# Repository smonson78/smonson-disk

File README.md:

# Smonson Disk
SD card (2x) to ACSI hard drive interface.

This project aims to develop a reliable and useful hard drive solution for Atari ST with two SD card sockets and a
battery-backed clock, satisfying the ACSI protocol, voltage, and timing requirements as given in available specifications.

Features:
- FPGA-controlled ACSI interface to ensure timing conforms to the specification
- One front-mounted removable SD card socket
- One internally-mounted microSD card socket
- SD cards running on a 24MHz SPI bus
- Battery-backed real-time clock
- GUI configuration from ST (once someone writes it...)
- Open-source, so if you want a feature all you have to do is write it and fit it into the 8KB of code space that is currently left!

## How to build and upload:

### Building the microcontroller firmware:
#### Prerequisites
You will need to install:
- A version of GCC that includes support for `avr128da` microcontrollers, cross-compiled for AVR (e.g. 5.4.0).
- A very recent version of avr-libc that has support for `avr128da` microcontrollers - https://www.nongnu.org/avr-libc/. You may need to get this from their github repo.
- A copy of the avr128da "atpack" from Microchip - go to https://packs.download.microchip.com/ and search for `avr128da`; "
Microchip AVR-Dx Series Device Support (2.4.286)" will pop open. Download this file, then change the file extension to `.zip` 
and unzip it into the directory `mcu-source/atpack`.
- (if you are using an Arduino as a programmer) A copy of jtag2updi from the githup repo here: https://github.com/ElTangas/jtag2updi. You will already have this on your system from when you programmed the device.

#### Building
1. Inside `mcu-source`:
1. Update the `Makefile` and set up `LIBC` variable to reflect the path to `avr-libc` on your system
1. Update the `AVRDUDE` variable to reflect your programmer setup (probably just the `avrdude.conf` path)
1. With the UPDI programmer connected, build the source and flash the microcontroller with `make flash`

### Building the FPGA configuration ROM image:

#### Prerequisites
You will need to install Quartus Lite which is a free download from Intel, although you will need to create an account.
Make sure you install MAX V family support
You will also need a "USB-Blaster" or compatible programmer.
If using Linux, you will very likely need to install a `udev` "rules" file for the programmer before it'll work.

#### Building
Just open the project in Quartus, go to "start compilation", then after it's compiled, open the programmer tool and program the chip. It should auto-detect the settings. If it doesn't find the USB Blaster hardware then it's probably udev's fault.

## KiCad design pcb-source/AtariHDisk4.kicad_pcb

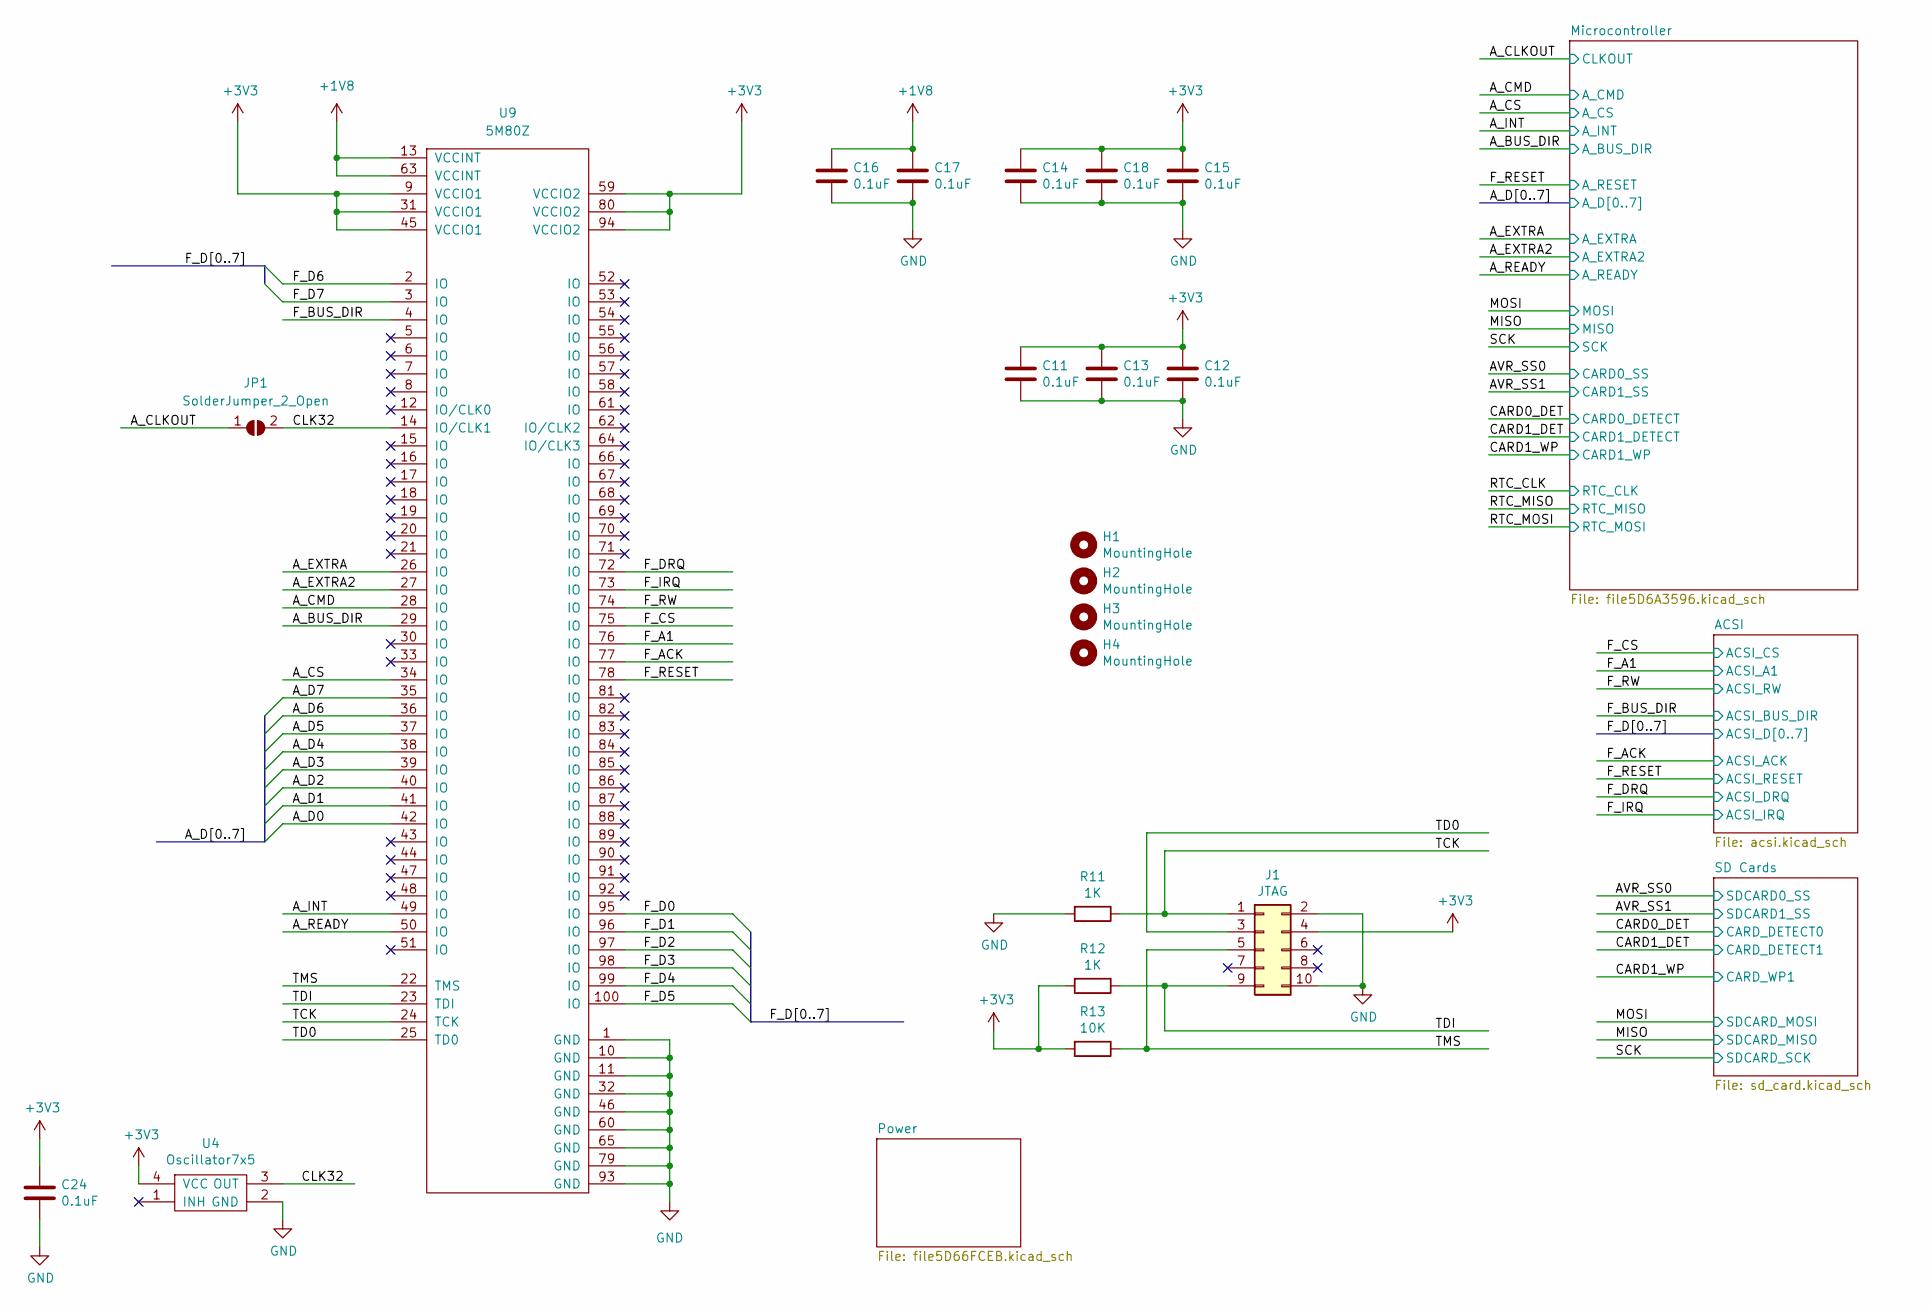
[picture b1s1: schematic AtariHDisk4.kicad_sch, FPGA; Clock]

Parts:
C11, C12, C13, C14, C15, C16, C17, C18, C24: 0.1uF; C_0603_1608Metric
H1, H2, H3, H4: MountingHole; Altronics_H0190_mounting_hole
J1: JTAG; PinHeader_2x05_P2.54mm_Vertical
JP1: SolderJumper_2_Open; SolderJumper-2_P1.3mm_Open_RoundedPad1.0x1.5mm
R11, R12: 1K; R_0805_2012Metric
R13: 10K; R_0805_2012Metric
U4: Oscillator7x5; XO_7x5
U9: 5M80Z; TQFP-100_14x14mm_P0.5mm

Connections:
+1V8: C16.1, C17.1, U9.13 (VCCINT), U9.63 (VCCINT); also elsewhere on the board
+3V3: C11.1, C12.1, C13.1, C14.1, C15.1, C18.1, C24.1, J1.4, R12.2, R13.2, U4.4 (VCC), U9.9 (VCCIO1), U9.31 (VCCIO1), U9.45 (VCCIO1), U9.59 (VCCIO2), U9.80 (VCCIO2), U9.94 (VCCIO2); also elsewhere on the board
/A_BUS_DIR: U9.29 (IO); also elsewhere on the board
/A_CLKOUT: JP1.1 (A); also elsewhere on the board
/A_CMD: U9.28 (IO); also elsewhere on the board
/A_CS: U9.34 (IO); also elsewhere on the board
/A_D0: U9.42 (IO); also elsewhere on the board
/A_D1: U9.41 (IO); also elsewhere on the board
/A_D2: U9.40 (IO); also elsewhere on the board
/A_D3: U9.39 (IO); also elsewhere on the board
/A_D4: U9.38 (IO); also elsewhere on the board
/A_D5: U9.37 (IO); also elsewhere on the board
/A_D6: U9.36 (IO); also elsewhere on the board
/A_D7: U9.35 (IO); also elsewhere on the board
/A_EXTRA: U9.26 (IO); also elsewhere on the board
/A_EXTRA2: U9.27 (IO); also elsewhere on the board
/A_INT: U9.49 (IO); also elsewhere on the board
/A_READY: U9.50 (IO); also elsewhere on the board
/CLK32: JP1.2 (B), U4.3 (OUT), U9.14 (IO/CLK1)
/F_A1: U9.76 (IO); also elsewhere on the board
/F_ACK: U9.77 (IO); also elsewhere on the board
/F_BUS_DIR: U9.4 (IO); also elsewhere on the board
/F_CS: U9.75 (IO); also elsewhere on the board
/F_D0: U9.95 (IO); also elsewhere on the board
/F_D1: U9.96 (IO); also elsewhere on the board
/F_D2: U9.97 (IO); also elsewhere on the board
/F_D3: U9.98 (IO); also elsewhere on the board
/F_D4: U9.99 (IO); also elsewhere on the board
/F_D5: U9.100 (IO); also elsewhere on the board
/F_D6: U9.2 (IO); also elsewhere on the board
/F_D7: U9.3 (IO); also elsewhere on the board
/F_DRQ: U9.72 (IO); also elsewhere on the board
/F_IRQ: U9.73 (IO); also elsewhere on the board
/F_RESET: U9.78 (IO); also elsewhere on the board
/F_RW: U9.74 (IO); also elsewhere on the board
/TCK: J1.1, R11.1, U9.24 (TCK)
/TD0: J1.3, U9.25 (TD0)
/TDI: J1.9, R12.1, U9.23 (TDI)
/TMS: J1.5, R13.1, U9.22 (TMS)
GND: C11.2, C12.2, C13.2, C14.2, C15.2, C16.2, C17.2, C18.2, C24.2, J1.2, J1.10, R11.2, U4.2 (GND), U9.1 (GND), U9.10 (GND), U9.11 (GND), U9.32 (GND), U9.46 (GND), U9.60 (GND), U9.65 (GND), U9.79 (GND), U9.93 (GND); also elsewhere on the board

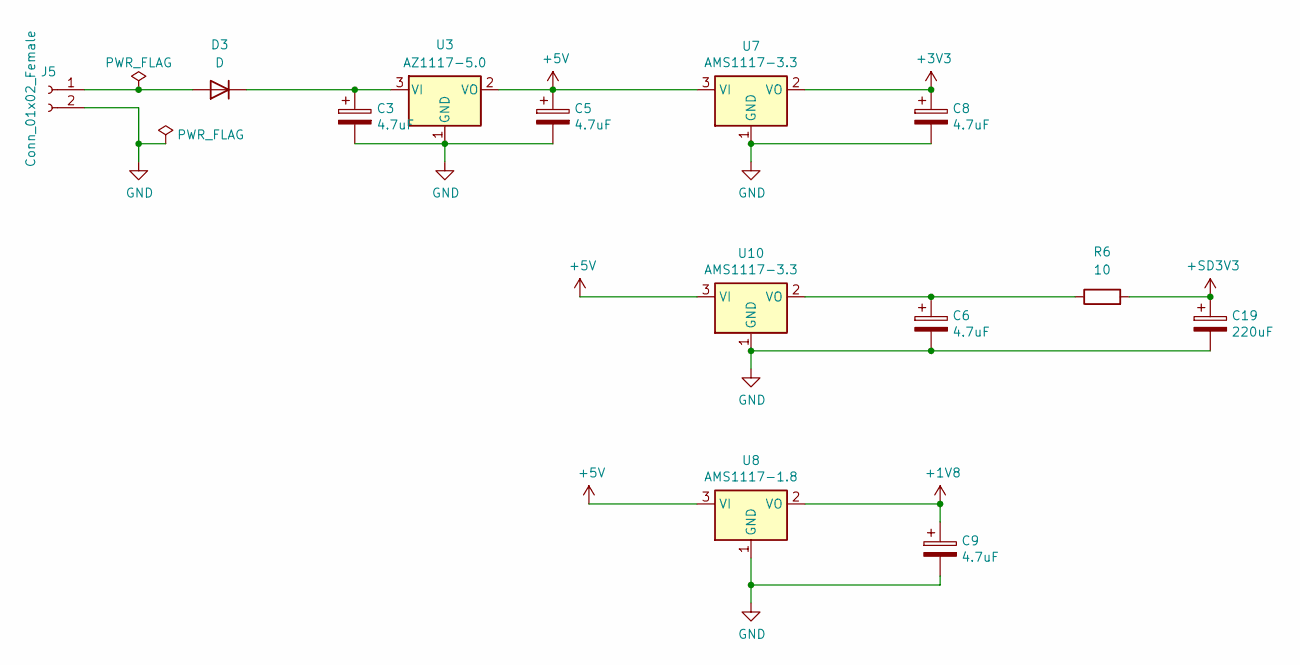
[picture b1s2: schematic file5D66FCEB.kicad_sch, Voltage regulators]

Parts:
C3: 4.7uF; CP_Radial_D6.3mm_P2.50mm
C5, C6, C8, C9: 4.7uF; C_1206_3216Metric
C19: 220uF; CP_Radial_D6.3mm_P2.50mm
D3: D; D_SMA
J5: Conn_01x02_Female; BarrelJack_Horizontal
R6: 10; R_0805_2012Metric
U3: AZ1117-5.0; SOT-223-3_TabPin2
U7, U10: AMS1117-3.3; SOT-223-3_TabPin2
U8: AMS1117-1.8; SOT-223-3_TabPin2

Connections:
+1V8: C9.1, U8.2 (VO); also elsewhere on the board
+3V3: C8.1, U7.2 (VO); also elsewhere on the board
+5V: C5.1, U3.2 (VO), U7.3 (VI), U8.3 (VI), U10.3 (VI); also elsewhere on the board
+SD3V3: C19.1, R6.2; also elsewhere on the board
GND: C3.2, C5.2, C6.2, C8.2, C9.2, C19.2, J5.2, U3.1 (GND), U7.1 (GND), U8.1 (GND), U10.1 (GND); also elsewhere on the board
unnamed: D3.2 (A), J5.1
unnamed: C3.1, D3.1 (K), U3.3 (VI)
unnamed: C6.1, R6.1, U10.2 (VO)

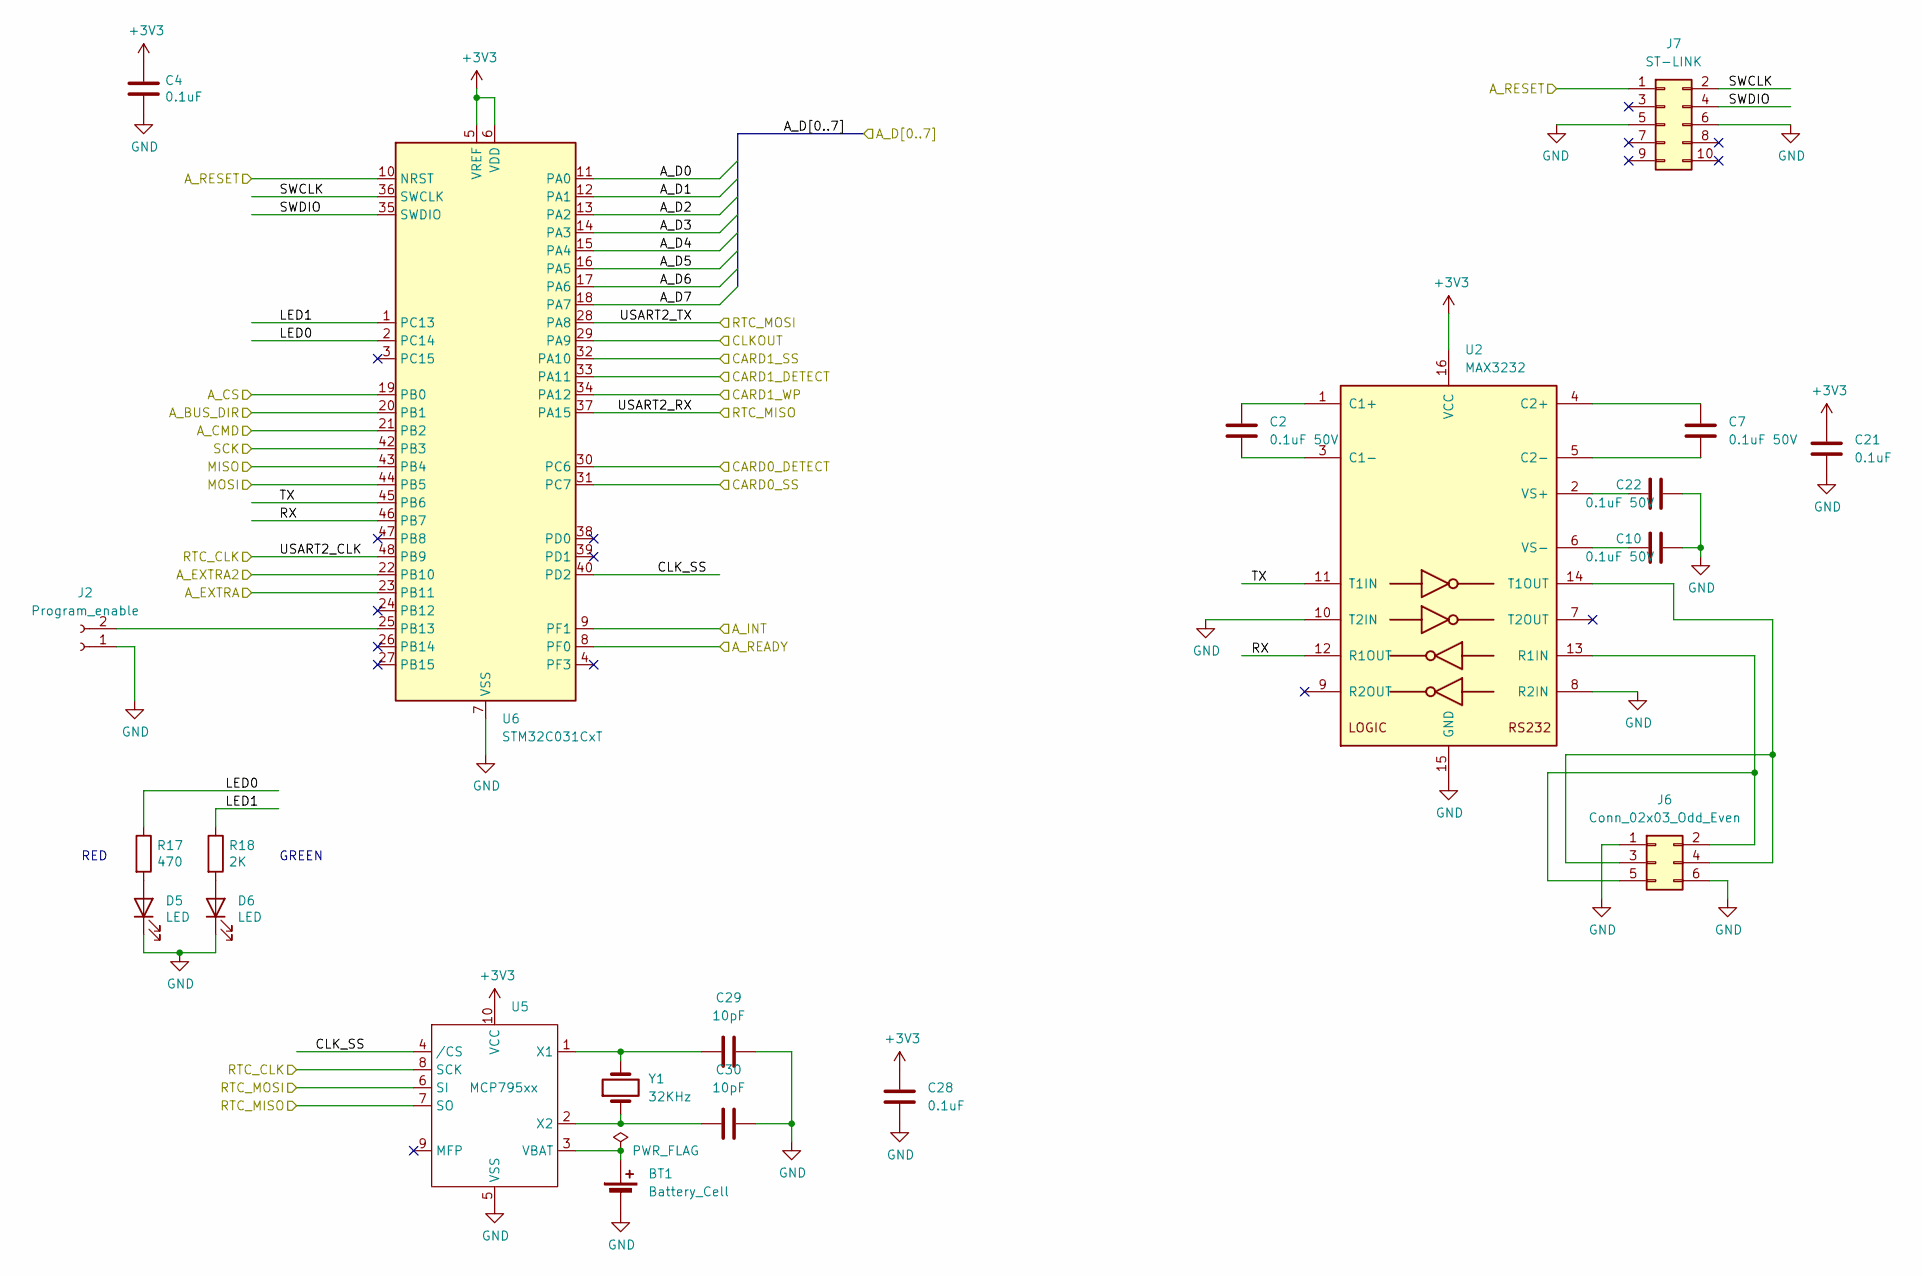
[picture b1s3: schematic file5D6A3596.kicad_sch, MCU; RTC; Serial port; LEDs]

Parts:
BT1: Battery_Cell; 712-BAT-HLD-002-SMT
C2, C7, C10, C22: 0.1uF 50V; C_0603_1608Metric
C4, C21, C28: 0.1uF; C_0603_1608Metric
C29, C30: 10pF; C_0603_1608Metric
D5, D6: LED; LED_D3.0mm_Horizontal_O1.27mm_Z2.0mm
J2: Program_enable; PinHeader_1x02_P2.54mm_Vertical
J6: Conn_02x03_Odd_Even; PinHeader_2x03_P2.54mm_Vertical
J7: ST-LINK; PinHeader_2x05_P2.54mm_Vertical
R17: 470; R_0805_2012Metric
R18: 2K; R_0805_2012Metric
U2: MAX3232; TSSOP-16_4.4x5mm_P0.65mm
U5: MCP795xx; MSOP-10_3x3mm_P0.5mm
U6: STM32C031CxT; LQFP-48_7x7mm_P0.5mm
Y1: 32KHz; Crystal_SMD_ECX_31B-2Pin_3.2x1.5mm

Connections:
+3V3: C4.1, C21.1, C28.1, U2.16 (VCC), U5.10 (VCC), U6.5 (VREF), U6.6 (VDD); also elsewhere on the board
/AVR_SS0: U6.31 (PC7); also elsewhere on the board
/AVR_SS1: U6.32 (PA10); also elsewhere on the board
/A_BUS_DIR: U6.20 (PB1); also elsewhere on the board
/A_CLKOUT: U6.29 (PA9); also elsewhere on the board
/A_CMD: U6.21 (PB2); also elsewhere on the board
/A_CS: U6.19 (PB0); also elsewhere on the board
/A_D0: U6.11 (PA0); also elsewhere on the board
/A_D1: U6.12 (PA1); also elsewhere on the board
/A_D2: U6.13 (PA2); also elsewhere on the board
/A_D3: U6.14 (PA3); also elsewhere on the board
/A_D4: U6.15 (PA4); also elsewhere on the board
/A_D5: U6.16 (PA5); also elsewhere on the board
/A_D6: U6.17 (PA6); also elsewhere on the board
/A_D7: U6.18 (PA7); also elsewhere on the board
/A_EXTRA: U6.23 (PB11); also elsewhere on the board
/A_EXTRA2: U6.22 (PB10); also elsewhere on the board
/A_INT: U6.9 (PF1); also elsewhere on the board
/A_READY: U6.8 (PF0); also elsewhere on the board
/CARD0_DET: U6.30 (PC6); also elsewhere on the board
/CARD1_DET: U6.33 (PA11); also elsewhere on the board
/CARD1_WP: U6.34 (PA12); also elsewhere on the board
/F_RESET: J7.1, U6.10 (NRST); also elsewhere on the board
/MISO: U6.43 (PB4); also elsewhere on the board
/MOSI: U6.44 (PB5); also elsewhere on the board
/Microcontroller/CLK_SS: U5.4 (/CS), U6.40 (PD2)
/Microcontroller/LED0: R17.1, U6.2 (PC14)
/Microcontroller/LED1: R18.1, U6.1 (PC13)
/Microcontroller/RX: U2.12 (R1OUT), U6.46 (PB7)
/Microcontroller/SWCLK: J7.2, U6.36 (SWCLK)
/Microcontroller/SWDIO: J7.4, U6.35 (SWDIO)
/Microcontroller/TX: U2.11 (T1IN), U6.45 (PB6)
/RTC_CLK: U5.8 (SCK), U6.48 (PB9)
/RTC_MISO: U5.7 (SO), U6.37 (PA15)
/RTC_MOSI: U5.6 (SI), U6.28 (PA8)
/SCK: U6.42 (PB3); also elsewhere on the board
GND: BT1.2 (-), C4.2, C10.2, C21.2, C22.2, C28.2, C29.2, C30.2, D5.1 (K), D6.1 (K), J2.1, J6.1, J6.6, J7.5, J7.6, U2.8 (R2IN), U2.10 (T2IN), U2.15 (GND), U5.5 (VSS), U6.7 (VSS); also elsewhere on the board
unnamed: BT1.1 (+), U5.3 (VBAT)
unnamed: D5.2 (A), R17.2
unnamed: D6.2 (A), R18.2
unnamed: J2.2, U6.25 (PB13)
unnamed: J6.2, J6.5, U2.13 (R1IN)
unnamed: J6.3, J6.4, U2.14 (T1OUT)
unnamed: C2.1, U2.1 (C1+)
unnamed: C2.2, U2.3 (C1-)
unnamed: C7.1, U2.4 (C2+)
unnamed: C7.2, U2.5 (C2-)
unnamed: C22.1, U2.2 (VS+)
unnamed: C10.1, U2.6 (VS-)
unnamed: C29.1, U5.1 (X1), Y1.2
unnamed: C30.1, U5.2 (X2), Y1.1

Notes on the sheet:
GREEN
RED

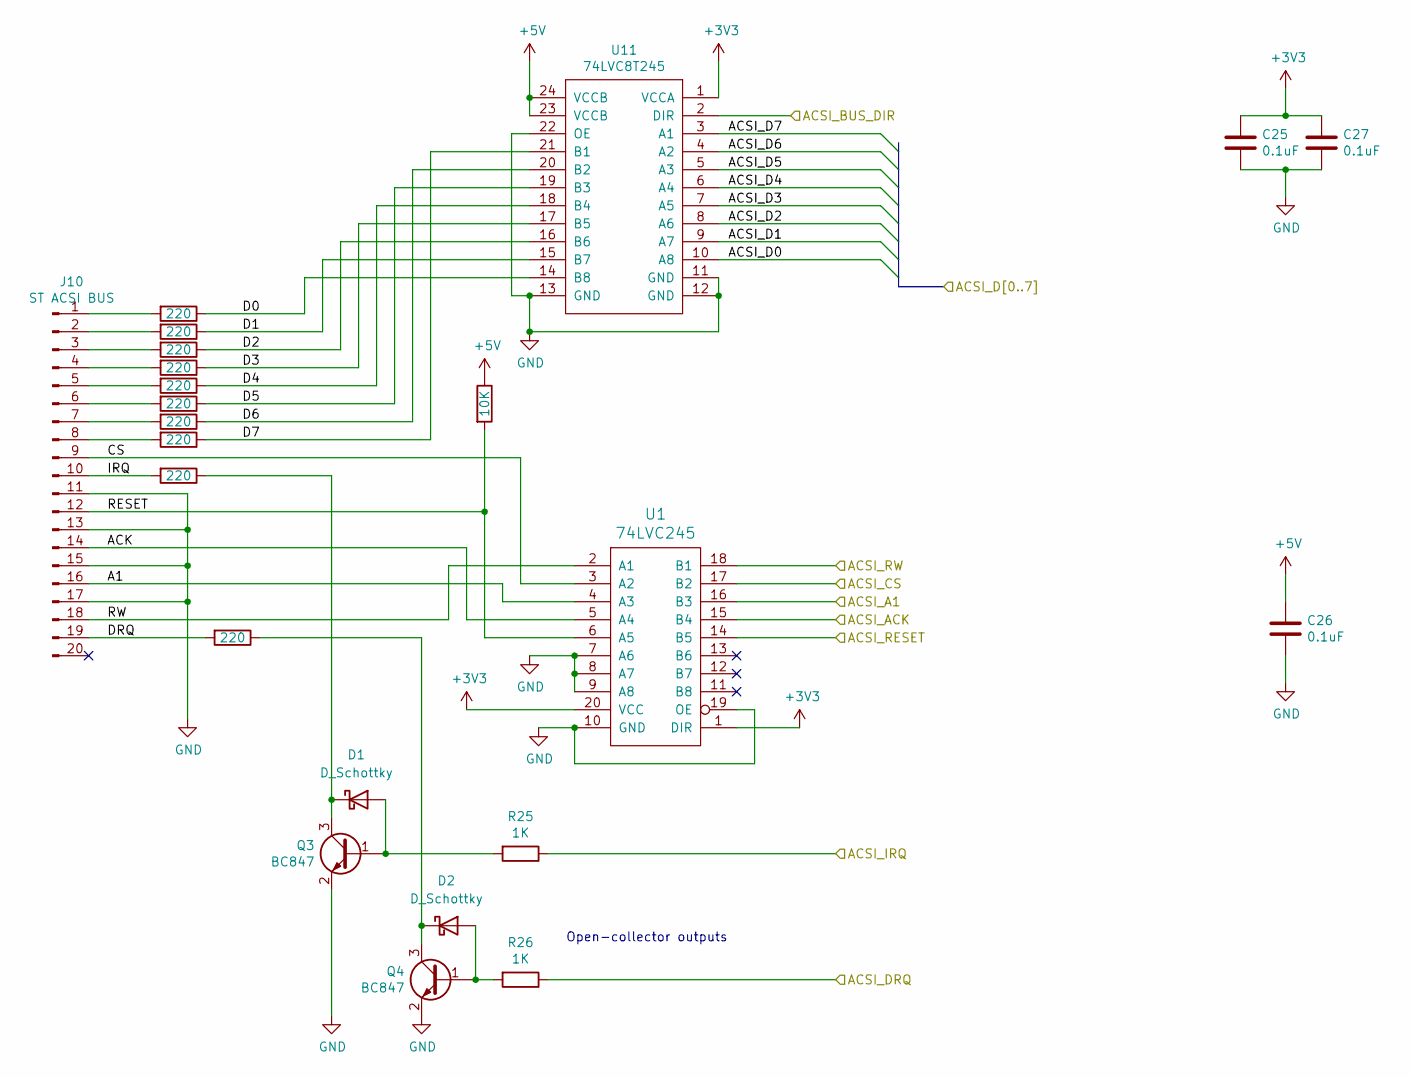
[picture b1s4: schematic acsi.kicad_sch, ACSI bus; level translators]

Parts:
C25, C26, C27: 0.1uF; C_0603_1608Metric
D1, D2: D_Schottky; D_1206_3216Metric
J10: ST ACSI BUS; IDC-Header_DB19_P2.54mm_Horizontal
Q3, Q4: BC847; SOT-23
R1, R2, R14, R15, R19, R20, R21, R22, R23, R24: 220; R_0805_2012Metric
R3: 10K; R_0805_2012Metric
R25, R26: 1K; R_0805_2012Metric
U1: 74LVC245; TSSOP-20_4.4x6.5mm_P0.65mm
U11: 74LVC8T245; TSSOP-24_4.4x7.8mm_P0.65mm

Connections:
+3V3: C25.1, C27.1, U1.1 (DIR), U1.20 (VCC), U11.1 (VCCA); also elsewhere on the board
+5V: C26.1, R3.1, U11.23 (VCCB), U11.24 (VCCB); also elsewhere on the board
/ACSI/A1: J10.16, U1.4 (A3)
/ACSI/ACK: J10.14, U1.5 (A4)
/ACSI/CS: J10.9, U1.3 (A2)
/ACSI/D0: R14.1, U11.14 (B8)
/ACSI/D1: R15.1, U11.15 (B7)
/ACSI/D2: R19.1, U11.16 (B6)
/ACSI/D3: R20.1, U11.17 (B5)
/ACSI/D4: R21.1, U11.18 (B4)
/ACSI/D5: R22.1, U11.19 (B3)
/ACSI/D6: R23.1, U11.20 (B2)
/ACSI/D7: R24.1, U11.21 (B1)
/ACSI/DRQ: J10.19, R2.2
/ACSI/IRQ: J10.10, R1.2
/ACSI/RESET: J10.12, R3.2, U1.6 (A5)
/ACSI/RW: J10.18, U1.2 (A1)
/F_A1: U1.16 (B3); also elsewhere on the board
/F_ACK: U1.15 (B4); also elsewhere on the board
/F_BUS_DIR: U11.2 (DIR); also elsewhere on the board
/F_CS: U1.17 (B2); also elsewhere on the board
/F_D0: U11.10 (A8); also elsewhere on the board
/F_D1: U11.9 (A7); also elsewhere on the board
/F_D2: U11.8 (A6); also elsewhere on the board
/F_D3: U11.7 (A5); also elsewhere on the board
/F_D4: U11.6 (A4); also elsewhere on the board
/F_D5: U11.5 (A3); also elsewhere on the board
/F_D6: U11.4 (A2); also elsewhere on the board
/F_D7: U11.3 (A1); also elsewhere on the board
/F_DRQ: R26.1; also elsewhere on the board
/F_IRQ: R25.1; also elsewhere on the board
/F_RESET: U1.14 (B5); also elsewhere on the board
/F_RW: U1.18 (B1); also elsewhere on the board
GND: C25.2, C26.2, C27.2, J10.11, J10.13, J10.15, J10.17, Q3.2 (E), Q4.2 (E), U1.7 (A6), U1.8 (A7), U1.9 (A8), U1.10 (GND), U1.19 (OE), U11.11 (GND), U11.12 (GND), U11.13 (GND), U11.22 (OE); also elsewhere on the board
unnamed: D1.2 (A), Q3.1 (B), R25.2
unnamed: D1.1 (K), Q3.3 (C), R1.1
unnamed: D2.2 (A), Q4.1 (B), R26.2
unnamed: D2.1 (K), Q4.3 (C), R2.1
unnamed: J10.1, R14.2
unnamed: J10.2, R15.2
unnamed: J10.3, R19.2
unnamed: J10.4, R20.2
unnamed: J10.5, R21.2
unnamed: J10.6, R22.2
unnamed: J10.7, R23.2
unnamed: J10.8, R24.2

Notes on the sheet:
Open-collector outputs

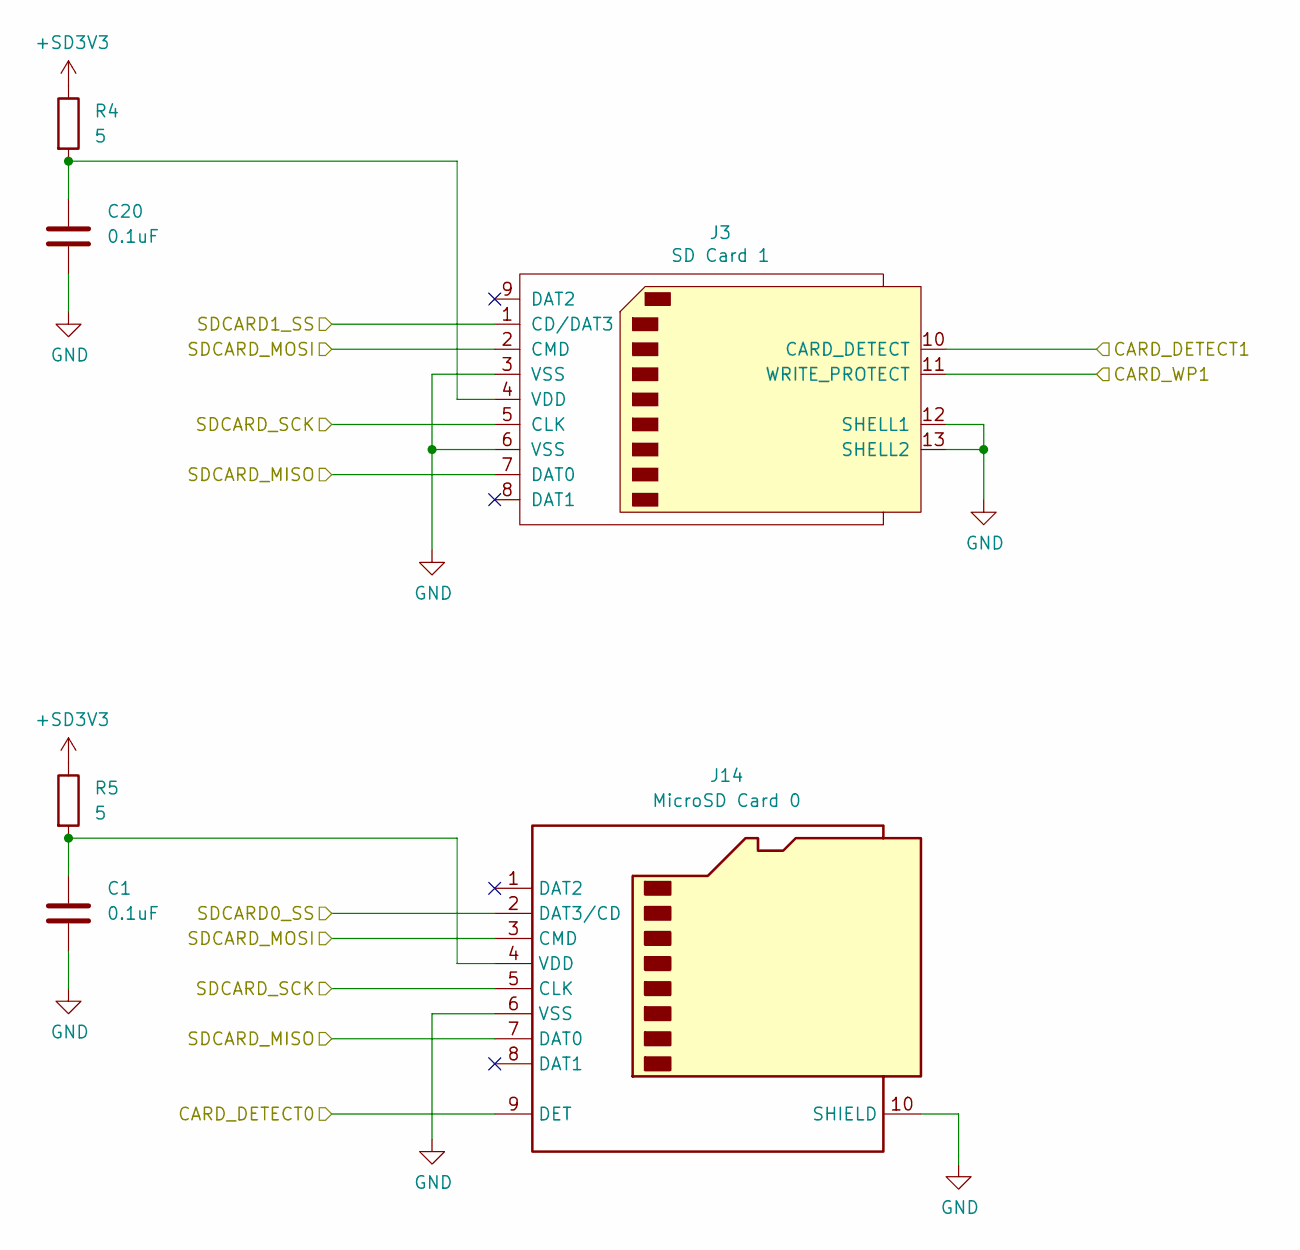
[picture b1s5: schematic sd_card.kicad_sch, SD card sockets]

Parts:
C1, C20: 0.1uF; C_0603_1608Metric
J3: SD Card 1; Amphenol_SD_Card_GSD090012SEU
J14: MicroSD Card 0; MicroSD_card_MSD-4-A
R4, R5: 5; R_0805_2012Metric

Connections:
+SD3V3: R4.1, R5.1; also elsewhere on the board
/AVR_SS0: J14.2 (DAT3/CD); also elsewhere on the board
/AVR_SS1: J3.1 (CD/DAT3); also elsewhere on the board
/CARD0_DET: J14.9 (DET); also elsewhere on the board
/CARD1_DET: J3.10 (CARD_DETECT); also elsewhere on the board
/CARD1_WP: J3.11 (WRITE_PROTECT); also elsewhere on the board
/MISO: J3.7 (DAT0), J14.7 (DAT0); also elsewhere on the board
/MOSI: J3.2 (CMD), J14.3 (CMD); also elsewhere on the board
/SCK: J3.5 (CLK), J14.5 (CLK); also elsewhere on the board
GND: C1.2, C20.2, J3.3 (VSS), J3.6 (VSS), J3.12 (SHELL1), J3.13 (SHELL2), J14.6 (VSS), J14.10 (SHIELD); also elsewhere on the board
unnamed: C20.1, J3.4 (VDD), R4.2
unnamed: C1.1, J14.4 (VDD), R5.2

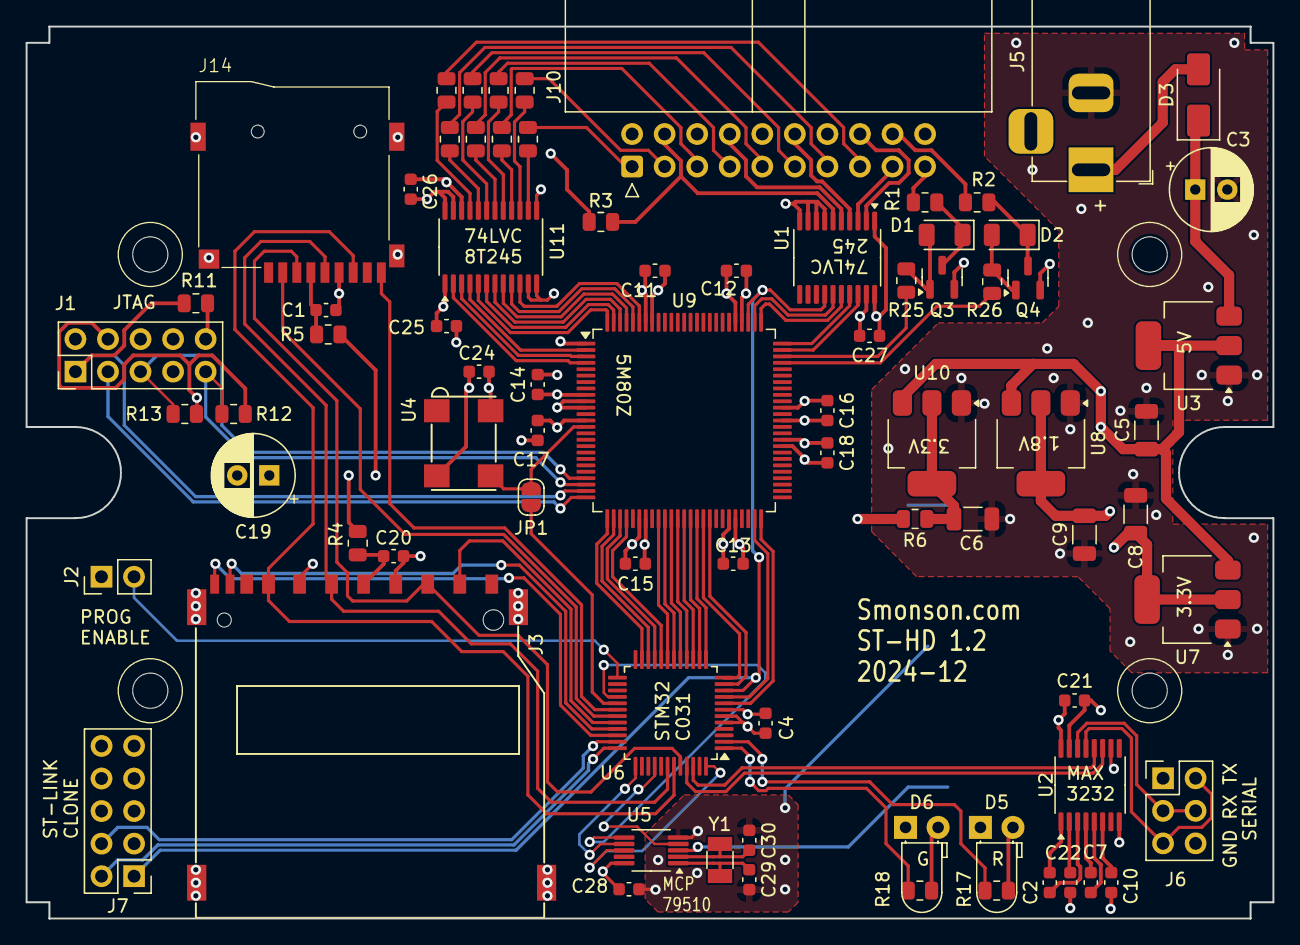
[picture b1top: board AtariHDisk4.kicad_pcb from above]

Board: 4 copper layers, 97.3 x 69.6 mm, 83 parts (1 on the bottom side), 106 nets.

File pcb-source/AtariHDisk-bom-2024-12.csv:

"Id";"Designator";"Footprint";"Quantity";"Designation";"Supplier and ref";
1;"C5,C8,C9,C6";"C_1206_3216Metric";4;"4.7uF";;;
2;"C3";"CP_Radial_D6.3mm_P2.50mm";1;"4.7uF";;;
3;"J1";"PinHeader_2x05_P2.54mm_Vertical";1;"JTAG";;;
4;"R12,R11,R25,R26";"R_0805_2012Metric";4;"1K";;;
5;"R13,R3";"R_0805_2012Metric";2;"10K";;;
6;"C18,C12,C17,C16,C14,C15,C21,C25,C1,C20,C26,C24,C27,C4,C11,C28,C13";"C_0603_1608Metric";17;"0.1uF";;;
7;"H4,H3,H1,H2";"Altronics_H0190_mounting_hole";4;"MountingHole";;;
8;"U7,U10";"SOT-223-3_TabPin2";2;"AMS1117-3.3";;;
9;"U8";"SOT-223-3_TabPin2";1;"AMS1117-1.8";;;
10;"U4";"XO_7x5";1;"Oscillator7x5";;;
11;"J5";"BarrelJack_Horizontal";1;"Conn_01x02_Female";;;
12;"U9";"TQFP-100_14x14mm_P0.5mm";1;"5M80Z";;;
13;"U5";"MSOP-10_3x3mm_P0.5mm";1;"MCP795xx";;;
14;"U3";"SOT-223-3_TabPin2";1;"AZ1117-5.0";;;
15;"D6,D5";"LED_D3.0mm_Horizontal_O1.27mm_Z2.0mm";2;"LED";;;
16;"C22,C10,C2,C7";"C_0603_1608Metric";4;"C";;;
17;"J2";"PinHeader_1x02_P2.54mm_Vertical";1;"Program_enable";;;
18;"R19,R20,R24,R23,R15,R2,R21,R14,R1,R22";"R_0805_2012Metric";10;"220";;;
19;"Q4,Q3";"SOT-23";2;"BC847";;;
20;"U2";"TSSOP-16_4.4x5mm_P0.65mm";1;"MAX3232";;;
21;"C19";"CP_Radial_D6.3mm_P2.50mm";1;"220uF";;;
22;"U6";"LQFP-48_7x7mm_P0.5mm";1;"STM32C031CxT";;;
23;"Y1";"Crystal_SMD_ECX_31B-2Pin_3.2x1.5mm";1;"32KHz";;;
24;"J14";"MicroSD_card_MSD-4-A";1;"MicroSD Card 0";;;
25;"D2,D1";"D_1206_3216Metric";2;"D_Schottky";;;
26;"R6";"R_0805_2012Metric";1;"10";;;
27;"R5,R4";"R_0805_2012Metric";2;"5";;;
28;"J3";"Amphenol_SD_Card_GSD090012SEU";1;"SD Card 1";;;
29;"U1";"TSSOP-20_4.4x6.5mm_P0.65mm";1;"74LVC245";;;
30;"R18";"R_0805_2012Metric";1;"2K";;;
31;"J6";"PinHeader_2x03_P2.54mm_Vertical";1;"Conn_02x03_Odd_Even";;;
32;"C29,C30";"C_0603_1608Metric";2;"3pF";;;
33;"R17";"R_0805_2012Metric";1;"470";;;
34;"D3";"D_SMA";1;"D";;;
35;"J7";"PinHeader_2x05_P2.54mm_Vertical";1;"ST-LINK";;;
36;"U11";"TSSOP-24_4.4x7.8mm_P0.65mm";1;"74LVC8T245";;;
37;"JP1";"SolderJumper-2_P1.3mm_Open_RoundedPad1.0x1.5mm";1;"SolderJumper_2_Open";;;
38;"J10";"IDC-Header_DB19_P2.54mm_Horizontal";1;"ST ACSI BUS";;;
39;"BT1";"712-BAT-HLD-002-SMT";1;"Battery_Cell";;;

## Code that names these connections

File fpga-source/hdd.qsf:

# -------------------------------------------------------------------------- #
#
# Copyright (C) 2019  Intel Corporation. All rights reserved.
# Your use of Intel Corporation's design tools, logic functions 
# and other software and tools, and any partner logic 
# functions, and any output files from any of the foregoing 
# (including device programming or simulation files), and any 
# associated documentation or information are expressly subject 
# to the terms and conditions of the Intel Program License 
# Subscription Agreement, the Intel Quartus Prime License Agreement,
# the Intel FPGA IP License Agreement, or other applicable license
# agreement, including, without limitation, that your use is for
# the sole purpose of programming logic devices manufactured by
# Intel and sold by Intel or its authorized distributors.  Please
# refer to the applicable agreement for further details, at
# https://fpgasoftware.intel.com/eula.
#
# -------------------------------------------------------------------------- #
#
# Quartus Prime
# Version 19.1.0 Build 670 09/22/2019 SJ Lite Edition
# Date created = 15:24:56  June 21, 2020
#
# -------------------------------------------------------------------------- #
#
# Notes:
#
# 1) The default values for assignments are stored in the file:
#		hdd_assignment_defaults.qdf
#    If this file doesn't exist, see file:
#		assignment_defaults.qdf
#
# 2) Altera recommends that you do not modify this file. This
#    file is updated automatically by the Quartus Prime software
#    and any changes you make may be lost or overwritten.
#
# -------------------------------------------------------------------------- #


set_global_assignment -name FAMILY "MAX V"
set_global_assignment -name DEVICE 5M80ZT100I5
set_global_assignment -name TOP_LEVEL_ENTITY hdd
set_global_assignment -name ORIGINAL_QUARTUS_VERSION 19.1.0
set_global_assignment -name PROJECT_CREATION_TIME_DATE "15:24:56  JUNE 21, 2020"
set_global_assignment -name LAST_QUARTUS_VERSION "25.1std.0 Lite Edition"
set_global_assignment -name PROJECT_OUTPUT_DIRECTORY output_files
set_global_assignment -name MIN_CORE_JUNCTION_TEMP "-40"
set_global_assignment -name MAX_CORE_JUNCTION_TEMP 125
set_global_assignment -name DEVICE_FILTER_PACKAGE "ANY QFP"
set_global_assignment -name ERROR_CHECK_FREQUENCY_DIVISOR "-1"
set_global_assignment -name VERILOG_FILE hdd.v
set_location_assignment PIN_96 -to f_data[1]
set_location_assignment PIN_95 -to f_data[0]
set_location_assignment PIN_98 -to f_data[3]
set_location_assignment PIN_97 -to f_data[2]
set_location_assignment PIN_100 -to f_data[5]
set_location_assignment PIN_99 -to f_data[4]
set_location_assignment PIN_3 -to f_data[7]
set_location_assignment PIN_2 -to f_data[6]
set_location_assignment PIN_4 -to f_bus_dir
set_location_assignment PIN_75 -to f_cs
set_location_assignment PIN_78 -to f_reset
set_location_assignment PIN_77 -to f_ack
set_location_assignment PIN_76 -to f_a1
set_location_assignment PIN_74 -to f_rw
set_location_assignment PIN_73 -to f_irq
set_location_assignment PIN_72 -to f_drq
set_location_assignment PIN_28 -to a_cmd
set_location_assignment PIN_42 -to a_data[0]
set_location_assignment PIN_34 -to a_cs
set_location_assignment PIN_41 -to a_data[1]
set_location_assignment PIN_29 -to a_bus_dir
set_location_assignment PIN_40 -to a_data[2]
set_location_assignment PIN_49 -to a_int
set_location_assignment PIN_39 -to a_data[3]
set_location_assignment PIN_38 -to a_data[4]
set_location_assignment PIN_37 -to a_data[5]
set_location_assignment PIN_36 -to a_data[6]
set_location_assignment PIN_35 -to a_data[7]
set_location_assignment PIN_14 -to clock
set_global_assignment -name POWER_PRESET_COOLING_SOLUTION "NO HEAT SINK WITH STILL AIR"
set_global_assignment -name TIMING_ANALYZER_MULTICORNER_ANALYSIS OFF
set_global_assignment -name NUM_PARALLEL_PROCESSORS 2
set_global_assignment -name ENABLE_OCT_DONE OFF
set_global_assignment -name USE_CONFIGURATION_DEVICE ON
set_global_assignment -name RESERVE_ALL_UNUSED_PINS "AS INPUT TRI-STATED WITH WEAK PULL-UP"
set_location_assignment PIN_50 -to a_ready
set_location_assignment PIN_26 -to a_extra
set_location_assignment PIN_27 -to a_extra_2

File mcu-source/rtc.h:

#ifndef __RTC_H
#define __RTC_H

#include <stdint.h>

#include "stdutil.h"

#define RTC_SS_PORT GPIOD
#define RTC_SS_PIN 2

// PA8 - Alternate Function 1
#define RTC_MOSI_PORT GPIOA
#define RTC_MOSI_BIT 8

// PA15 - Alternate Function 1
#define RTC_MISO_PORT GPIOA
#define RTC_MISO_BIT 15

// PB9 - Alternate Function 1
#define RTC_CLK_PORT GPIOB
#define RTC_CLK_BIT 9

#define MCP7951_CLRRAM 0b01010100
#define MCP7951_READ 0b00010011
#define MCP7951_WRITE 0b00010010

typedef struct {
  uint16_t year;
  uint8_t month;
  uint8_t day;
  uint8_t hour;
  uint8_t minute;
  uint8_t second;
} datetime_t;

void rtc_setup();
void rtc_read(uint8_t addr, uint8_t *dest, uint8_t len);
void rtc_write(uint8_t addr, uint8_t *data, uint8_t len);
void rtc_set(datetime_t *datetime);
void rtc_get(datetime_t *dest);

#endif

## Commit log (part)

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2024-04-12 Initial import of WIP microcontroller source
2024-04-12 Added README
2024-04-12 Added PCB source files
2024-04-13 Added fus config to Makefile to fix reset pin Fixed RXC interrupt enable flag in serial code Allow debug level to be changed any time
2024-04-23 Fixed a few issues with SD card timeouts Made SD cards detect changes
2024-04-23 Added FPGA source code (latest)
2024-04-23 Removed device programmer config file and added it to .gitignore
2024-04-24 Start writing a settime program
2024-04-24 Hopefully finished a basic settime.ttp command to program the RTC
2024-04-25 Part of clock working
2024-04-25 Updates for settime.ttp
2024-04-27 Set/set clock vendor-specific commands
2024-04-27 Finished RTC read/write commands
2024-04-27 Fixed bug in capacity check
2024-04-29 Finished settine/gettime
2024-04-29 Experimental: interrupt-driven double-buffered SPI comms for SD card
2024-04-29 Use buffered mode. Increases data rate to 724KB/s
2024-04-30 Experiment: double-buffered data mode
2024-04-30 Fixed data read edge
2024-04-30 Use double-buffered mode and slightly speed up avr to fpga writing
2024-04-30 unrolled 510-byte inner loop
2024-05-01 Fix off-by-one in READ CAPACITY (10)
2024-05-01 Fixed 2 typos; deleted the debug LED functions from fpga_comm.h
2024-05-01 FPGA testbench updates
2024-05-01 Switched the avr128da to an stm32c031
2024-05-10 Starting point for STM32 chip
2024-05-10 Commented out AVR-specific bits so that the rest of the code can be compiled for ARM
2024-05-11 Got interrupt-driven serial to work on Cortex-M3 dev board. Copying that code in here.
2024-05-12 Further updates - was able to do a test of the SD card.
2024-05-18 Final board setup that was sent to production
2024-06-01 New changes as I slowly port the code to the new board
2024-06-02 Improved workingness and macro support
2024-06-02 Working serial
2024-06-02 Block working, progress towards getting SPI working
2024-06-03 Mode code improvements. Testing SD card now. RTC isn't coming online properly yet with 4pF crystals
2024-06-04 Finished porting, but ovbiously it's not gonna work first try!
2024-06-05 Not sure
2024-06-10 Fixed compilation on laptop by including .rodata in binary
2024-06-10 Added FPGA pin assignments
2024-06-10 Removed A_RESET on FPGA
2024-06-10 Working version, albeit slowly
2024-06-13 DMA implementation working
2024-06-13 Prototype code off my laptop which is now at the point of working
2024-06-13 STM32C01 version, now in a working state (#6)
    Code for V2 board, proven and now working.
2024-12-17 1.2 version with 2 SPI buses
